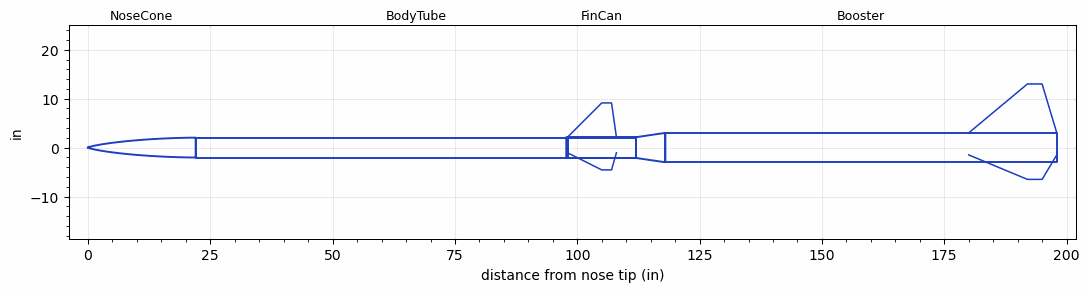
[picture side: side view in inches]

<RASAeroDocument>
 <FileVersion>2</FileVersion>
 <RocketDesign>
  <NoseCone>
   <Length>22</Length>
   <Diameter>4.06</Diameter>
   <Shape>LV-Haack</Shape>
   <Location>0</Location>
  </NoseCone>
  <BodyTube>
   <Length>90</Length>
   <Diameter>4.06</Diameter>
   <Location>22</Location>
  </BodyTube>
  <FinCan>
   <Length>14</Length>
   <Diameter>4.25</Diameter>
   <InsideDiameter>4.06</InsideDiameter>
   <Location>112</Location>
   <ShoulderLength>0.25</ShoulderLength>
   <Offset>-14</Offset>
   <Fin>
    <Count>3</Count>
    <Chord>10</Chord>
    <Span>7</Span>
    <SweepDistance>7</SweepDistance>
    <TipChord>2</TipChord>
    <Thickness>0.125</Thickness>
    <Location>14</Location>
    <AirfoilSection>Hexagonal</AirfoilSection>
    <FX1>0.125</FX1>
    <FX3>0.125</FX3>
   </Fin>
  </FinCan>
  <Booster>
   <Length>80</Length>
   <Diameter>6</Diameter>
   <InsideDiameter>4.25</InsideDiameter>
   <Location>112</Location>
   <ShoulderLength>6</ShoulderLength>
   <Fin>
    <Count>3</Count>
    <Chord>18</Chord>
    <Span>10</Span>
    <SweepDistance>12</SweepDistance>
    <TipChord>3</TipChord>
    <Thickness>0.125</Thickness>
    <Location>18</Location>
    <AirfoilSection>Hexagonal</AirfoilSection>
    <FX1>0.125</FX1>
    <FX3>0.125</FX3>
   </Fin>
  </Booster>
  <Surface>Smooth Paint</Surface>
  <ModifiedBarrowman>True</ModifiedBarrowman>
  <Turbulence>True</Turbulence>
  <UseBooster1>False</UseBooster1>
  <UseBooster2>False</UseBooster2>
 </RocketDesign>
 <LaunchSite>
  <Altitude>4500</Altitude>
  <Pressure>0</Pressure>
  <RodAngle>0</RodAngle>
  <RodLength>25</RodLength>
  <Temperature>85</Temperature>
  <WindSpeed>5</WindSpeed>
 </LaunchSite>
 <Recovery>
  <Altitude1>1000</Altitude1>
  <Altitude2>1000</Altitude2>
  <DeviceType1>Parachute</DeviceType1>
  <DeviceType2>Parachute</DeviceType2>
  <Event1>True</Event1>
  <Event2>True</Event2>
  <Size1>36</Size1>
  <Size2>60</Size2>
  <EventType1>Apogee</EventType1>
  <EventType2>Altitude</EventType2>
  <CD1>2.3</CD1>
  <CD2>2.3</CD2>
 </Recovery>
 <SimulationList>
  <Simulation>
   <SustainerEngine>O3400-IM-P  (CTI)</SustainerEngine>
   <SustainerLaunchWt>63.5</SustainerLaunchWt>
   <SustainerNozzleDiameter>4</SustainerNozzleDiameter>
   <SustainerCG>59</SustainerCG>
   <SustainerIgnitionDelay>5</SustainerIgnitionDelay>
   <Booster1Engine>P-7700  (CTI)</Booster1Engine>
   <Booster1LaunchWt>204</Booster1LaunchWt>
   <Booster1SeparationDelay>1</Booster1SeparationDelay>
   <Booster1IgnitionDelay>0</Booster1IgnitionDelay>
   <Booster1CG>126</Booster1CG>
   <Booster1NozzleDiameter>6</Booster1NozzleDiameter>
   <IncludeBooster1>True</IncludeBooster1>
   <Booster2Delay>0</Booster2Delay>
   <IncludeBooster2>False</IncludeBooster2>
   <TimetoApogee>171.5296</TimetoApogee>
   <MaxAltitude>425379.7</MaxAltitude>
   <MaxVelocity>5204.256</MaxVelocity>
  </Simulation>
  <Simulation>
   <SustainerEngine>O3400-IM-P  (CTI)</SustainerEngine>
   <SustainerLaunchWt>66</SustainerLaunchWt>
   <SustainerNozzleDiameter>4</SustainerNozzleDiameter>
   <SustainerCG>59</SustainerCG>
   <SustainerIgnitionDelay>5</SustainerIgnitionDelay>
   <Booster1Engine>P-7700  (CTI)</Booster1Engine>
   <Booster1LaunchWt>210</Booster1LaunchWt>
   <Booster1SeparationDelay>1</Booster1SeparationDelay>
   <Booster1IgnitionDelay>0</Booster1IgnitionDelay>
   <Booster1CG>125</Booster1CG>
   <Booster1NozzleDiameter>6</Booster1NozzleDiameter>
   <IncludeBooster1>True</IncludeBooster1>
   <Booster2Delay>0</Booster2Delay>
   <IncludeBooster2>False</IncludeBooster2>
   <TimetoApogee>164.8133</TimetoApogee>
   <MaxAltitude>391572.6</MaxAltitude>
   <MaxVelocity>4982.859</MaxVelocity>
  </Simulation>
 </SimulationList>
</RASAeroDocument>
